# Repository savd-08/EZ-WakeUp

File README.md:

# EZ-WakeUp
Alarma despertadora con capacidades de detección de humo.

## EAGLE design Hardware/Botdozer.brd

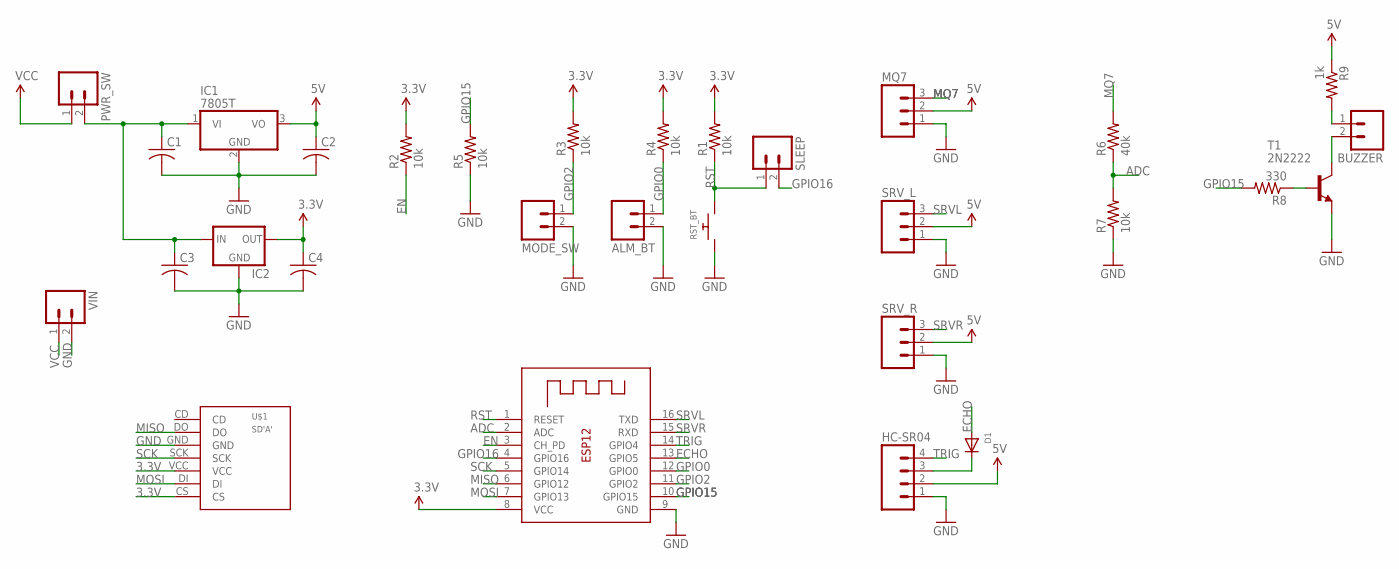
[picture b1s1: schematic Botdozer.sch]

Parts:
ALM_BT: M02PTH; 1X02
BUZZER: M02PTH; 1X02
C1, C2, C3, C4: C-US025-025X050; C025-025X050
D1: DIODEDO-1N4148; DO-1N4148
HC-SR04: M04PTH; 1X04
IC1: 7805T; TO220H
IC2: 78XXL
MODE_SW: M02PTH; 1X02
MQ7: M03PTH; 1X03
PWR_SW: M02PTH; 1X02
R1, R2, R3, R4, R5, R7: 10k; 0207/10
R6: 40k; 0207/10
R8: 330; 0207/10
R9: 1k; 0207/10
RST_BT: SWITCH_PUSHBUTTONEVQ-PE; TACT_PANA-EVQ
SLEEP: M02PTH; 1X02
SRV_L: M03PTH; 1X03
SRV_R: M03PTH; 1X03
T1: 2N2222; TO92-EBC-OVAL
U$1: SD'A'; SD_BR
VIN: M02PTH; 1X02
X1: ESP-12

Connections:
3.3V: C4.1, IC2.OUT, R1.2, R2.2, R3.2, R4.2, U$1.CS, U$1.VCC, X1.8 (VCC)
5V: C2.1, HC-SR04.2, IC1.3 (VO), MQ7.2, R9.1, SRV_L.2, SRV_R.2
ADC: R6.1, R7.2, X1.2 (ADC)
ECHO: D1.A, X1.13 (GPIO5)
EN: R2.1, X1.3 (CH_PD)
GND: ALM_BT.2, C1.2, C2.2, C3.2, C4.2, HC-SR04.1, IC1.2 (GND), IC2.GND, MODE_SW.2, MQ7.1, R5.1, R7.1, RST_BT.P$1, SRV_L.1, SRV_R.1, T1.E, U$1.GND, VIN.2, X1.9 (GND)
GPIO0: ALM_BT.1, R4.1, X1.12 (GPIO0)
GPIO2: MODE_SW.1, R3.1, X1.11 (GPIO2)
GPIO15: R5.2, R8.2, X1.10 (GPIO15)
GPIO16: SLEEP.2, X1.4 (GPIO16)
MISO: U$1.DO, X1.6 (GPIO12)
MOSI: U$1.DI, X1.7 (GPIO13)
MQ7: MQ7.3, R6.2
unnamed: BUZZER.2, T1.C
unnamed: R8.1, T1.B
unnamed: C1.1, C3.1, IC1.1 (VI), IC2.IN, PWR_SW.2
unnamed: BUZZER.1, R9.2
unnamed: D1.C, HC-SR04.3
RST: R1.1, RST_BT.P$2, SLEEP.1, X1.1 (RESET)
SCK: U$1.SCK, X1.5 (GPIO14)
SRVL: SRV_L.3, X1.16 (TXD)
SRVR: SRV_R.3, X1.15 (RXD)
TRIG: HC-SR04.4, X1.14 (GPIO4)
VCC: PWR_SW.1, VIN.1

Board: 2 copper layers, 30 parts (0 on the bottom side), 24 nets, no tracks yet.

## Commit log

2016-10-14 Agrega diseño de PCB para ESP-12 y HUZZAH ESP8266
2016-10-21 Se agrega codigo fuente de app movil
2016-10-21 Implementación inicial del firmware del dispositivo
2016-10-23 Versión inicial del servidor. Requiere probar. No tengo ESP8266
2016-10-24 Agrega archivos para fabricación de PCB (Gerber, G-code)
2016-10-25 Agrega rutina de alarma, mensajes de debugging, lectura de sensor ultrasónico, servos, buzzer
2016-10-26 Agrega soporte para carga de configuración de EEPROM, rutina de alarma
2016-10-27 Ejemplo de escritura
    Logger guardado en la tarjeta SD
2016-10-28 Nueva versión del server. Red estable y se reciben solicitudes. Sensor de humo en proceso de calibración
2016-10-29 adicionado el lector de SD
2016-10-29 adicionado el lector SD
2016-11-01 Se obtiene concentración de humo en ppm
2016-11-01 Arregla conflictos
2016-11-03 Completa funcionalidad del firmware
2016-11-04 Server versión final
2016-11-04 Agrega nueva versión del server al firmware
2016-11-05 Versión final de todo
2016-11-09 test

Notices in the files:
parts and their libraries:
SparkFun-Connectors: Licensing: Creative Commons ShareAlike 4.0 International - https://creativecommons.org/licenses/by-sa/4.0
